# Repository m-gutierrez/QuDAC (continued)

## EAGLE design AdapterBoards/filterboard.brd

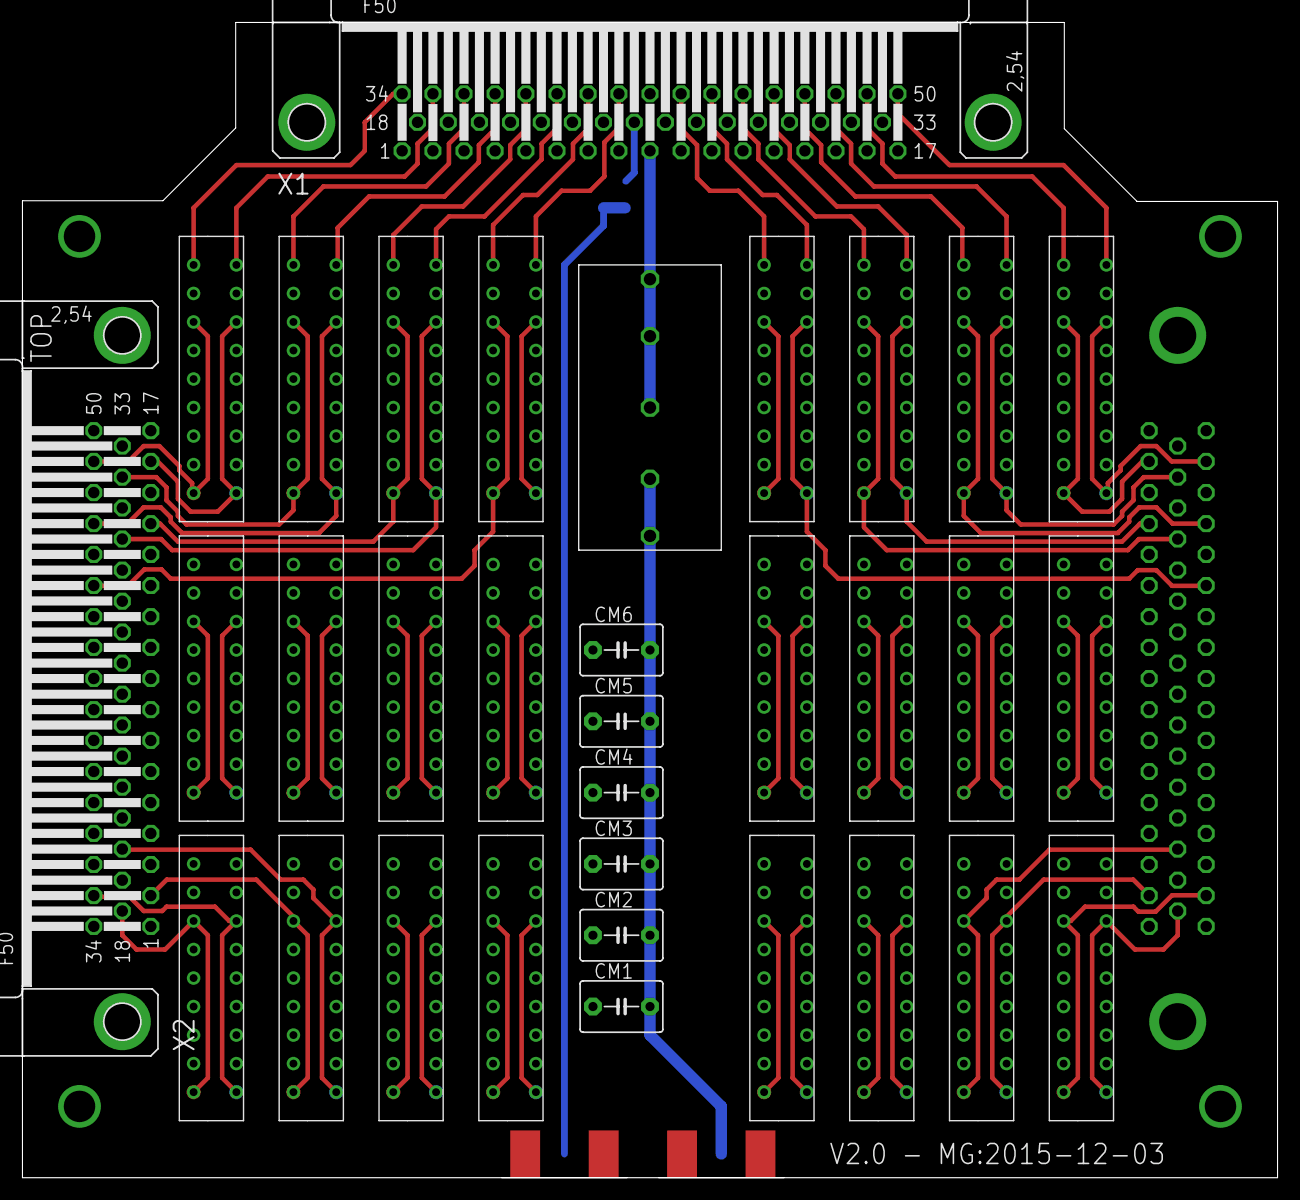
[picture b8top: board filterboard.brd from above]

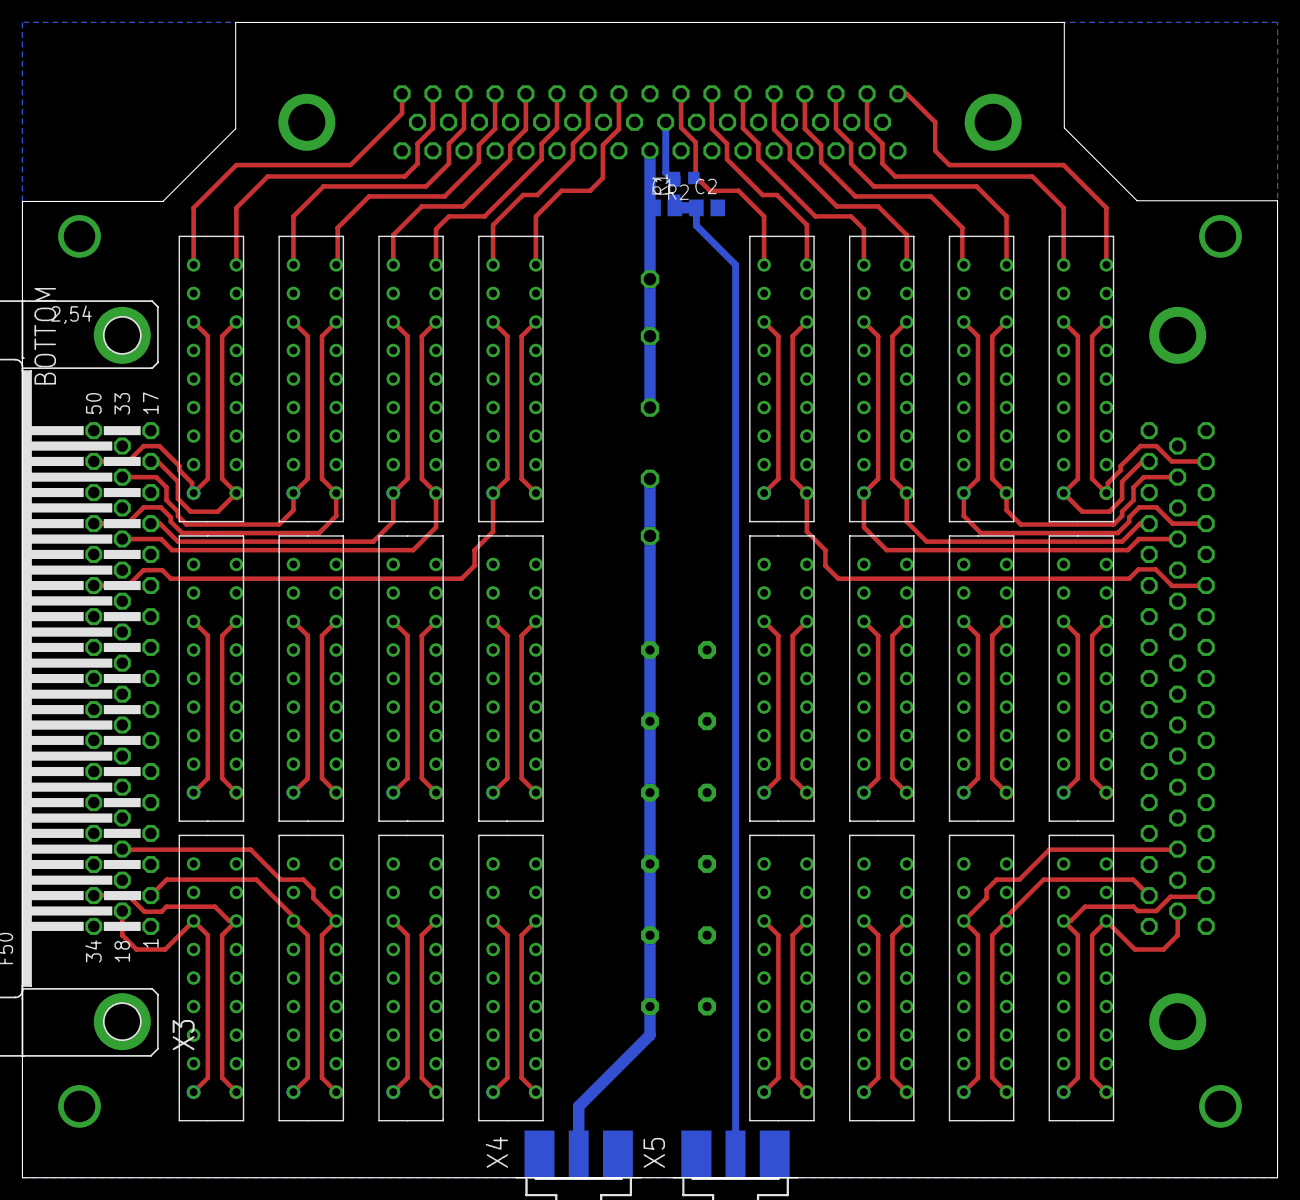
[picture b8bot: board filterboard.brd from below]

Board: 4 copper layers, 111.8 x 102.9 mm, 64 parts (31 on the bottom side), 101 nets.

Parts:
C1: 1pF; C0805
C2: 1000pF; C0805
CM1, CM2, CM3, CM4, CM5, CM6: C5B4.5
R1, R2: R0603
U$1, U$2, U$3, U$4, U$5, U$6, U$7, U$8, U$9, U$10, U$11, U$12, U$13, U$14, U$15, U$16, U$17, U$18, U$19, U$20, U$21, U$22, U$23, U$24, U$25, U$26, U$27, U$28, U$29, U$30, U$31, U$32, U$33, U$34, U$35, U$36, U$37, U$38, U$39, U$40, U$41, U$42, U$43, U$44, U$45, U$46, U$47, U$48: COILCRAFT-LC7POLE
U$49: XINDUCTOR
X1, X2, X3: F50HP
X4: RF IN; J502-ND-142-0711-821/826
X5: RF tap; J502-ND-142-0711-821/826

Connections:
GND: C2.2, CM1.1, CM2.1, CM3.1, CM4.1, CM5.1, CM6.1, R2.1, U$1.GND0, U$1.GND1, U$1.GND2, U$1.GND3, U$1.NC0, U$1.NC1, U$2.GND0, U$2.GND1, U$2.GND2, U$2.GND3, U$2.NC0, U$2.NC1, U$3.GND0, U$3.GND1, U$3.GND2, U$3.GND3, U$3.NC0, U$3.NC1, U$4.GND0, U$4.GND1, U$4.GND2, U$4.GND3, U$4.NC0, U$4.NC1, U$5.GND0, U$5.GND1, U$5.GND2, U$5.GND3, U$5.NC0, U$5.NC1, U$6.GND0, U$6.GND1, U$6.GND2, U$6.GND3, U$6.NC0, U$6.NC1, U$7.GND0, U$7.GND1, U$7.GND2, U$7.GND3, U$7.NC0, U$7.NC1, U$8.GND0, U$8.GND1, U$8.GND2, U$8.GND3, U$8.NC0, U$8.NC1, U$9.GND0, U$9.GND1, U$9.GND2, U$9.GND3, U$9.NC0, U$9.NC1, U$10.GND0, U$10.GND1, U$10.GND2, U$10.GND3, U$10.NC0, U$10.NC1, U$11.GND0, U$11.GND1, U$11.GND2, U$11.GND3, U$11.NC0, U$11.NC1, U$12.GND0, U$12.GND1, U$12.GND2, U$12.GND3, U$12.NC0, U$12.NC1, U$13.GND0, U$13.GND1, U$13.GND2, U$13.GND3, U$13.NC0, U$13.NC1, U$14.GND0, U$14.GND1, U$14.GND2, U$14.GND3, U$14.NC0, U$14.NC1, U$15.GND0, U$15.GND1, U$15.GND2, U$15.GND3, U$15.NC0, U$15.NC1, U$16.GND0, U$16.GND1, U$16.GND2, U$16.GND3, U$16.NC0, U$16.NC1, U$17.GND0, U$17.GND1, U$17.GND2, U$17.GND3, U$17.NC0, U$17.NC1, U$18.GND0, U$18.GND1, U$18.GND2, U$18.GND3, U$18.NC0, U$18.NC1, U$19.GND0, U$19.GND1, U$19.GND2, U$19.GND3, U$19.NC0, U$19.NC1, U$20.GND0, U$20.GND1, U$20.GND2, U$20.GND3, U$20.NC0, U$20.NC1, U$21.GND0, U$21.GND1, U$21.GND2, U$21.GND3, U$21.NC0, U$21.NC1, U$22.GND0, U$22.GND1, U$22.GND2, U$22.GND3, U$22.NC0, U$22.NC1, U$23.GND0, U$23.GND1, U$23.GND2, U$23.GND3, U$23.NC0, U$23.NC1, U$24.GND0, U$24.GND1, U$24.GND2, U$24.GND3, U$24.NC0, U$24.NC1, U$25.GND0, U$25.GND1, U$25.GND2, U$25.GND3, U$25.NC0, U$25.NC1, U$26.GND0, U$26.GND1, U$26.GND2, U$26.GND3, U$26.NC0, U$26.NC1, U$27.GND0, U$27.GND1, U$27.GND2, U$27.GND3, U$27.NC0, U$27.NC1, U$28.GND0, U$28.GND1, U$28.GND2, U$28.GND3, U$28.NC0, U$28.NC1, U$29.GND0, U$29.GND1, U$29.GND2, U$29.GND3, U$29.NC0, U$29.NC1, U$30.GND0, U$30.GND1, U$30.GND2, U$30.GND3, U$30.NC0, U$30.NC1, U$31.GND0, U$31.GND1, U$31.GND2, U$31.GND3, U$31.NC0, U$31.NC1, U$32.GND0, U$32.GND1, U$32.GND2, U$32.GND3, U$32.NC0, U$32.NC1, U$33.GND0, U$33.GND1, U$33.GND2, U$33.GND3, U$33.NC0, U$33.NC1, U$34.GND0, U$34.GND1, U$34.GND2, U$34.GND3, U$34.NC0, U$34.NC1, U$35.GND0, U$35.GND1, U$35.GND2, U$35.GND3, U$35.NC0, U$35.NC1, U$36.GND0, U$36.GND1, U$36.GND2, U$36.GND3, U$36.NC0, U$36.NC1, U$37.GND0, U$37.GND1, U$37.GND2, U$37.GND3, U$37.NC0, U$37.NC1, U$38.GND0, U$38.GND1, U$38.GND2, U$38.GND3, U$38.NC0, U$38.NC1, U$39.GND0, U$39.GND1, U$39.GND2, U$39.GND3, U$39.NC0, U$39.NC1, U$40.GND0, U$40.GND1, U$40.GND2, U$40.GND3, U$40.NC0, U$40.NC1, U$41.GND0, U$41.GND1, U$41.GND2, U$41.GND3, U$41.NC0, U$41.NC1, U$42.GND0, U$42.GND1, U$42.GND2, U$42.GND3, U$42.NC0, U$42.NC1, U$43.GND0, U$43.GND1, U$43.GND2, U$43.GND3, U$43.NC0, U$43.NC1, U$44.GND0, U$44.GND1, U$44.GND2, U$44.GND3, U$44.NC0, U$44.NC1, U$45.GND0, U$45.GND1, U$45.GND2, U$45.GND3, U$45.NC0, U$45.NC1, U$46.GND0, U$46.GND1, U$46.GND2, U$46.GND3, U$46.NC0, U$46.NC1, U$47.GND0, U$47.GND1, U$47.GND2, U$47.GND3, U$47.NC0, U$47.NC1, U$48.GND0, U$48.GND1, U$48.GND2, U$48.GND3, U$48.NC0, U$48.NC1, X1.G1, X1.G2, X2.1, X2.3, X2.5, X2.7, X2.9, X2.11, X2.13, X2.15, X2.17, X2.19, X2.21, X2.23, X2.25, X2.27, X2.29, X2.31, X2.33, X2.34, X2.36, X2.38, X2.40, X2.42, X2.44, X2.46, X2.48, X2.50, X3.1, X3.3, X3.5, X3.7, X3.9, X3.11, X3.13, X3.15, X3.17, X3.19, X3.21, X3.23, X3.25, X3.27, X3.29, X3.31, X3.33, X3.34, X3.36, X3.38, X3.40, X3.42, X3.44, X3.46, X3.48, X3.50, X4.G@1, X4.G@2, X5.G@1, X5.G@2
unnamed: C1.2, C2.1, X5.1
unnamed: R1.2, X1.25
S$1: U$49.INPUT3, U$49.OUTPUT1, U$49.OUTPUT2, X1.9
S$2: CM1.2, CM2.2, CM3.2, CM4.2, CM5.2, CM6.2, U$49.INPUT, U$49.INPUT2, X4.1
S$3: U$7.FILTER-OUTPUT, X1.34
S$4: U$9.FILTER-OUTPUT, X1.35
S$5: U$8.FILTER-OUTPUT, X1.36
S$6: U$22.FILTER-OUTPUT, X1.37
S$7: U$21.FILTER-OUTPUT, X1.38
S$8: U$42.FILTER-OUTPUT, X1.39
S$9: U$5.FILTER-OUTPUT, X1.40
S$10: U$12.FILTER-OUTPUT, X1.18
S$11: U$43.FILTER-OUTPUT, X1.19
S$12: U$36.FILTER-OUTPUT, X1.20
S$13: U$2.FILTER-OUTPUT, X1.21
S$14: U$3.FILTER-OUTPUT, X1.22
S$15: U$4.FILTER-OUTPUT, X1.23
S$16: U$6.FILTER-OUTPUT, X1.24
S$17: U$47.FILTER-OUTPUT, X1.41
S$18: U$46.FILTER-OUTPUT, X1.42
S$19: U$35.FILTER-OUTPUT, X1.1
S$20: U$18.FILTER-OUTPUT, X1.2
S$21: U$19.FILTER-OUTPUT, X1.3
S$22: U$20.FILTER-OUTPUT, X1.4
S$23: U$41.FILTER-OUTPUT, X1.5
S$24: U$11.FILTER-OUTPUT, X1.6
S$25: U$34.FILTER-OUTPUT, X1.7
S$26: U$10.FILTER-OUTPUT, X1.8
S$27: U$35.FILTER-INPUT, U$35.NC2, X2.18
S$28: U$18.FILTER-INPUT, U$18.NC2, X2.35
S$29: U$19.FILTER-INPUT, U$19.NC2, X2.2
S$30: U$20.NC2, X2.20
S$31: U$41.FILTER-INPUT, U$41.NC2, X2.37
S$32: U$11.FILTER-INPUT, U$11.NC2, X2.4
S$33: U$34.FILTER-INPUT, U$34.NC2, X2.22
S$34: U$10.FILTER-INPUT, U$10.NC2, X2.39
S$35: U$12.FILTER-INPUT, U$12.NC2, X2.6
S$36: U$43.FILTER-INPUT, U$43.NC2, X2.24
S$37: U$36.FILTER-INPUT, U$36.NC2, X2.41
S$38: U$2.FILTER-INPUT, U$2.NC2, X2.8
S$39: U$3.FILTER-INPUT, U$3.NC2, X2.26
S$40: U$4.FILTER-INPUT, U$4.NC2, X2.43
S$41: U$6.FILTER-INPUT, U$6.NC2, X2.10
S$42: U$46.FILTER-INPUT, U$46.NC2, X2.28
S$43: U$47.FILTER-INPUT, U$47.NC2, X2.12
S$44: U$5.FILTER-INPUT, U$5.NC2, X2.45
S$45: U$42.FILTER-INPUT, U$42.NC2, X2.30
S$46: U$21.FILTER-INPUT, U$21.NC2, X2.14
S$47: U$22.FILTER-INPUT, U$22.NC2, X2.47
S$48: U$8.FILTER-INPUT, U$8.NC2, X2.32
S$49: U$9.FILTER-INPUT, U$9.NC2, X2.16
S$50: U$7.FILTER-INPUT, U$7.NC2, X2.49
S$51: U$17.FILTER-OUTPUT, X1.50
S$52: U$24.FILTER-OUTPUT, X1.49
S$53: U$23.FILTER-OUTPUT, X1.48
S$54: U$32.FILTER-OUTPUT, X1.47
S$55: U$31.FILTER-OUTPUT, X1.46
S$56: U$40.FILTER-OUTPUT, X1.45
S$57: U$15.FILTER-OUTPUT, X1.44
S$58: U$27.FILTER-OUTPUT, X1.33
S$59: U$44.FILTER-OUTPUT, X1.32
S$60: U$38.FILTER-OUTPUT, X1.31
S$61: U$1.FILTER-OUTPUT, X1.30
S$62: U$13.FILTER-OUTPUT, X1.29
S$63: U$14.FILTER-OUTPUT, X1.28
S$64: U$16.FILTER-OUTPUT, X1.27
S$65: U$48.FILTER-OUTPUT, X1.43
S$66: U$45.FILTER-OUTPUT, X1.26
S$67: U$37.FILTER-OUTPUT, X1.17
S$68: U$28.FILTER-OUTPUT, X1.16
S$69: U$29.FILTER-OUTPUT, X1.15
S$70: U$30.FILTER-OUTPUT, X1.14
S$71: U$39.FILTER-OUTPUT, X1.13
S$72: U$26.FILTER-OUTPUT, X1.12
S$73: U$33.FILTER-OUTPUT, X1.11
S$74: U$25.FILTER-OUTPUT, X1.10
S$75: U$37.FILTER-INPUT, U$37.NC2, X3.18
S$76: U$28.FILTER-INPUT, U$28.NC2, X3.35
S$77: U$29.FILTER-INPUT, U$29.NC2, X3.2
S$78: U$30.NC2, X3.20
S$79: U$39.FILTER-INPUT, U$39.NC2, X3.37
S$80: U$26.FILTER-INPUT, U$26.NC2, X3.4
S$81: U$33.FILTER-INPUT, U$33.NC2, X3.22
S$82: U$25.FILTER-INPUT, U$25.NC2, X3.39
S$83: U$27.FILTER-INPUT, U$27.NC2, X3.6
S$84: U$44.FILTER-INPUT, U$44.NC2, X3.24
S$85: U$38.FILTER-INPUT, U$38.NC2, X3.41
S$86: U$1.FILTER-INPUT, U$1.NC2, X3.8
S$87: U$13.FILTER-INPUT, U$13.NC2, X3.26
S$88: U$14.FILTER-INPUT, U$14.NC2, X3.43
S$89: U$16.FILTER-INPUT, U$16.NC2, X3.10
S$90: U$45.FILTER-INPUT, U$45.NC2, X3.28
S$91: U$48.FILTER-INPUT, U$48.NC2, X3.12
S$92: U$15.FILTER-INPUT, U$15.NC2, X3.45
S$93: U$40.FILTER-INPUT, U$40.NC2, X3.30
S$94: U$31.FILTER-INPUT, U$31.NC2, X3.14
S$95: U$32.FILTER-INPUT, U$32.NC2, X3.47
S$96: U$23.FILTER-INPUT, U$23.NC2, X3.32
S$97: U$24.FILTER-INPUT, U$24.NC2, X3.16
S$98: U$17.FILTER-INPUT, U$17.NC2, X3.49

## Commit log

2016-08-18 Added eagle files for QuDAC and supporting boards
2016-08-18 Updated gitignore to include eagle files / exclude backups
2016-08-18 Updated ignore ignore files.
2016-08-18 Added readme
2016-08-18 organized, updated README
2016-08-18 testing readme images
2016-08-18 Updated readme, reorganized some files
2016-08-18 updated readme, re-organization
2016-08-18 Updated readme image
2016-08-18 image didn't get added / updated?
2016-08-18 read me tables?
2016-08-18 tables again
2016-08-18 readme
2017-06-08 changed photo
